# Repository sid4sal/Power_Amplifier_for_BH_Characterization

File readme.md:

# Design and Implementation of High Bandwidth Power Amplifier for B-H Characterization of Magnetic Materials

## Project Overview

The High Bandwidth Power Amplifier is a device for magnetic materials engineers to obtain B-H characterization of magnetic materials at low as well as high frequencies. It is a transformer-less multi-stage direct-coupled linear power amplifier for the characterization of magnetic cores at various frequencies.

The amplifier operates from 50 Hz to 250 kHz with a gain of approximately 4.6 (13.2 dB). It can handle an input power voltage up to ±60 V, allowing the reference signal to be given up to 12-13 V. The current rating of the amplifier is up to 2.5-3 A (continuous).

The user manual and all the required files can be found at this repo.

## Folder Descriptions

- *B-H_curve_plotting_MatLab*: Contains MATLAB files for plotting the simulated B-H curve of the toroid.
  
- *CAD_Outer_Casing_Design*: Includes the design of the outer casing in JPEG format.
  
- *Circuit_Design_and_simulation_results*: Contains the circuit diagrams, stages, and frequency response simulations in both KiCad and Proteus formats. It also includes the PCB design and 3D view, along with potential improvements.
  
- *Demo_and_Experiment_Videos*: Holds videos demonstrating the initial testing of the breadboard circuit, testing of the amplifier on the toroid core, and PCB testing.
  
- *Experiment Results*: Contains experimental results like B-H characteristic data, observed frequency response with load, and primary and secondary voltages at different frequencies.
  
- *Frequency_Response_Observed_vs_Simulated*: Compares the observed and simulated frequency responses in KiCad and Proteus.
  
- *PCB_Design_and_Circuit_Simulation_KiCad*: Placeholder for the KiCad files related to PCB design and circuit simulation.
  
- *Simulation_Proteus*: Placeholder for the Proteus simulation files.

## Additional Documents

- *Circuit_Diagram.png*: Circuit diagram of the power amplifier.
  
- *PCB.jpeg* & *PCB2.jpeg*: Images of the PCB design.
  
- *Project_Problem_Statement.docx*: Detailed problem statement of the project.
  
- *Toroidal_core_design_and_calculation.pdf*: Design and calculations related to the toroidal core.
  
- *Toroid_Core_Detailed_Calculations.pdf*: Detailed calculations for the toroidal core.
  
- *User Manual for Power Amplifier.pdf*: User manual for operating the power amplifier.

Feel free to reach out to me for any clarifications or further details. my contact details can be found inside the user manual.

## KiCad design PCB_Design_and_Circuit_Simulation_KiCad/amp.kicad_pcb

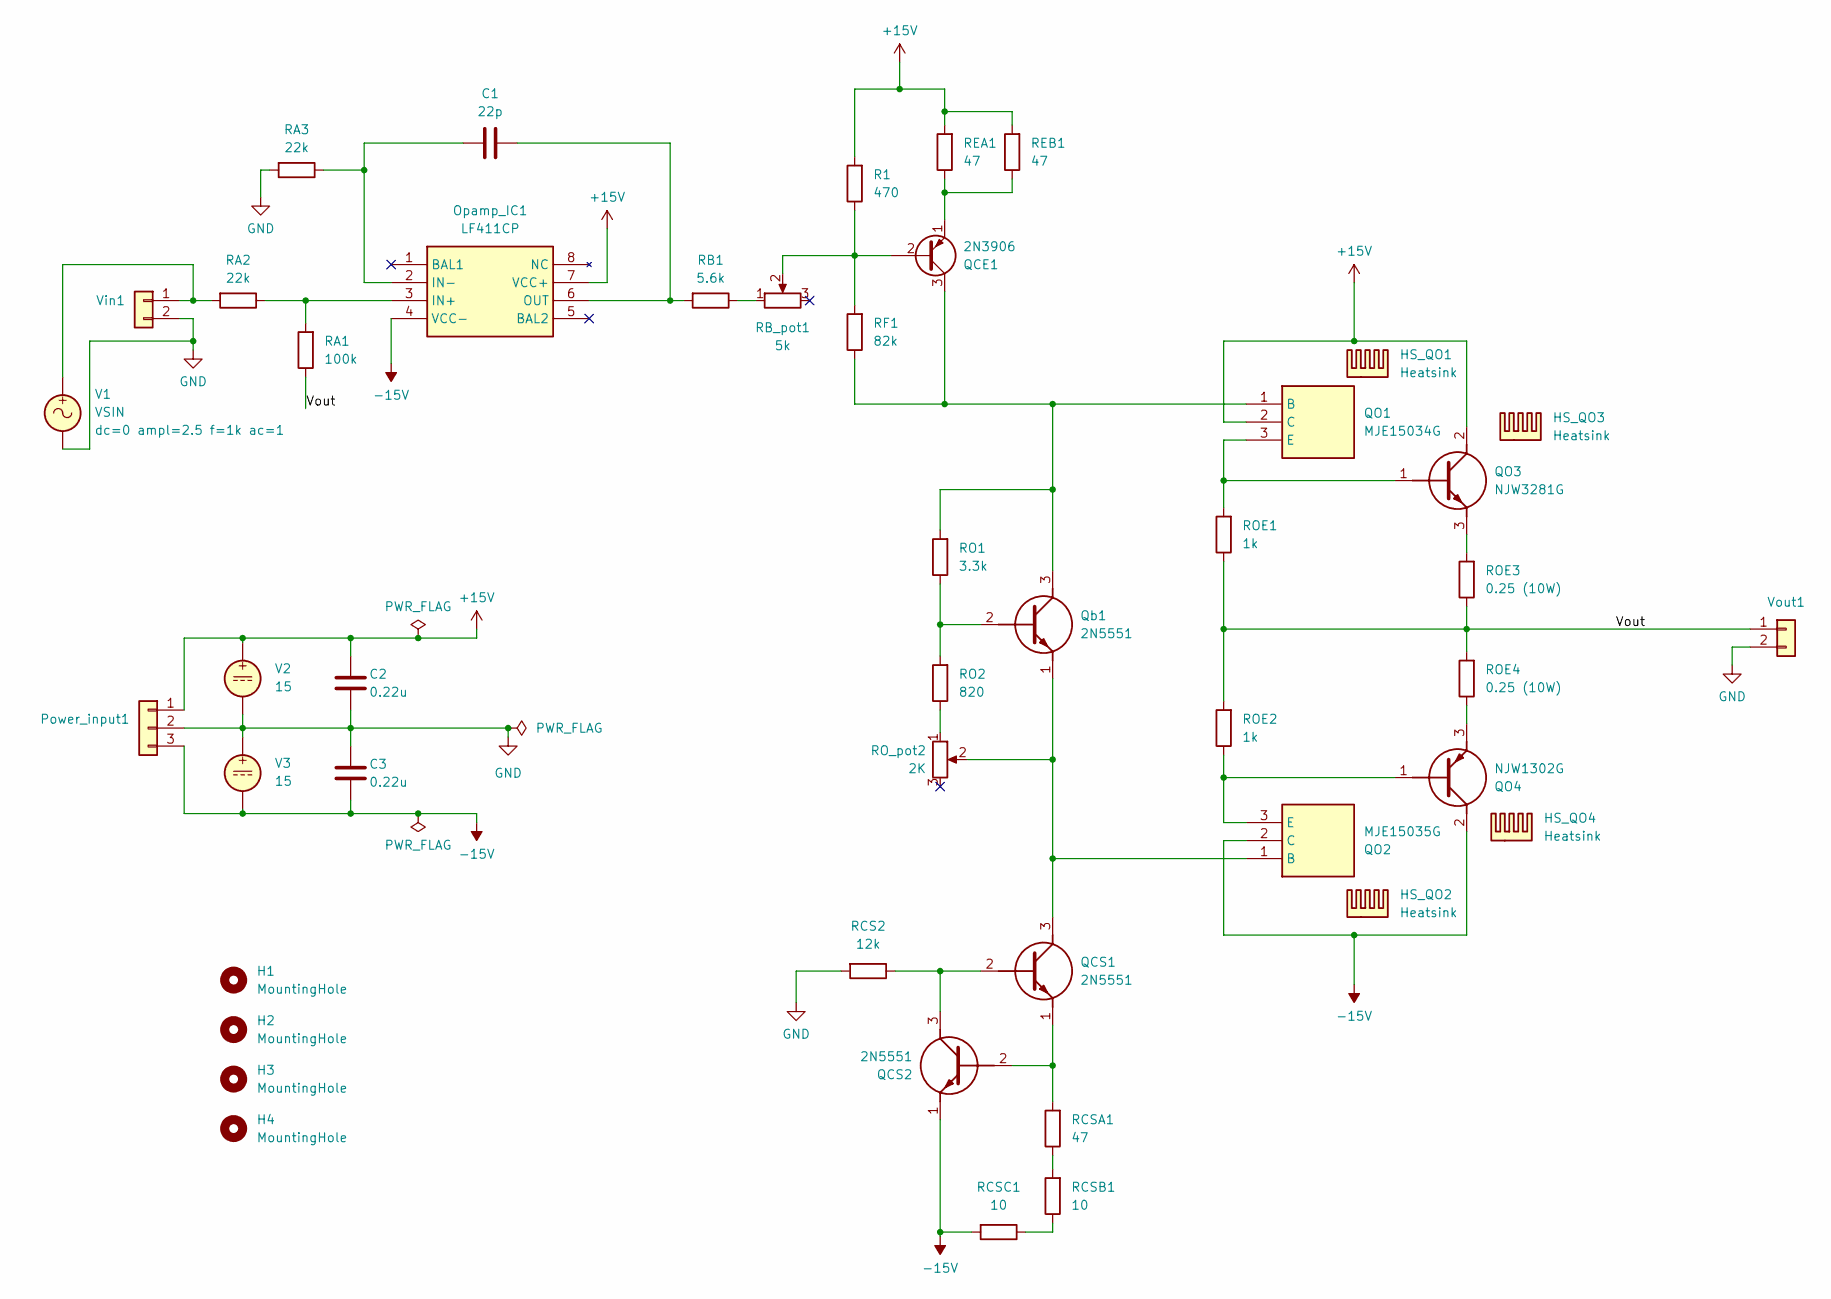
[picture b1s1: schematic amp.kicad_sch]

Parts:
C1: 22p; C_Disc_D3.8mm_W2.6mm_P2.50mm
C2, C3: 0.22u; C_Rect_L7.0mm_W2.0mm_P5.00mm
H1, H2, H3, H4: MountingHole; MountingHole_3mm
HS_QO1, HS_QO2: Heatsink; Heatsink_Stonecold_HS-S03_13.21x12.7mm
HS_QO3, HS_QO4: Heatsink; Heatsink_Fischer_SK129-STS_42x25mm_2xDrill2.5mm
Opamp_IC1: LF411CP; DIP-8_W7.62mm_Socket_LongPads; Mouser Part Number 595-LF411CP
Power_input1: Conn_01x03; PinHeader_1x03_P2.54mm_Vertical
QCE1: 2N3906; TO-92L_Inline_Wide
QCS1, QCS2: 2N5551; TO-92L_Inline_Wide; Mouser Part Number 863-2N5551
QO1: MJE15034G; TO254P483X1010X2035-3P; Mouser Part Number 863-MJE15034G
QO2: MJE15035G; TO254P483X1010X2035-3P; Mouser Part Number 863-MJE15035G
QO3: NJW3281G; TO545P500X1560X2380-3P; Mouser Part Number 863-NJW3281G
QO4: NJW1302G; TO545P500X1560X2380-3P; Mouser Part Number 863-NJW1302G
Qb1: 2N5551; TO-92L_Inline_Wide; Mouser Part Number 863-2N5551
R1: 470; R_Axial_DIN0309_L9.0mm_D3.2mm_P12.70mm_Horizontal
RA1: 100k; R_Axial_DIN0309_L9.0mm_D3.2mm_P12.70mm_Horizontal
RA2, RA3: 22k; R_Axial_DIN0309_L9.0mm_D3.2mm_P12.70mm_Horizontal
RB1: 5.6k; R_Axial_DIN0309_L9.0mm_D3.2mm_P12.70mm_Horizontal
RB_pot1: 5k; Potentiometer_Bourns_3386P_Vertical
RCS2: 12k; R_Axial_DIN0309_L9.0mm_D3.2mm_P12.70mm_Horizontal
RCSA1: 47; R_Axial_DIN0309_L9.0mm_D3.2mm_P12.70mm_Horizontal
RCSB1: 10; R_Axial_DIN0309_L9.0mm_D3.2mm_P12.70mm_Horizontal
RCSC1: 10; R_Axial_DIN0309_L9.0mm_D3.2mm_P12.70mm_Horizontal
REA1: 47; R_Axial_DIN0309_L9.0mm_D3.2mm_P12.70mm_Horizontal
REB1: 47; R_Axial_DIN0309_L9.0mm_D3.2mm_P12.70mm_Horizontal
RF1: 82k; R_Axial_DIN0309_L9.0mm_D3.2mm_P12.70mm_Horizontal
RO1: 3.3k; R_Axial_DIN0309_L9.0mm_D3.2mm_P12.70mm_Horizontal
RO2: 820; R_Axial_DIN0309_L9.0mm_D3.2mm_P12.70mm_Horizontal
ROE1, ROE2: 1k; R_Axial_DIN0309_L9.0mm_D3.2mm_P12.70mm_Horizontal
ROE3, ROE4: 0.25 (10W); R_Axial_Power_L38.0mm_W9.0mm_P40.64mm
RO_pot2: 2K; Potentiometer_Bourns_3386P_Vertical
V1: VSIN
V2, V3: 15
Vin1: Conn_01x02; PinHeader_1x02_P2.54mm_Vertical
Vout1: Conn_01x02; PinHeader_1x02_P2.54mm_Vertical

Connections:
+15V: C2.1, Opamp_IC1.7 (VCC+), Power_input1.1, QO1.2 (C), QO3.2 (C), R1.2, REA1.2, REB1.2, V2.1
-15V: C3.2, Opamp_IC1.4 (VCC-), Power_input1.3, QCS2.1 (E), QO2.2 (C), QO4.2 (C), RCSC1.2, V3.2
/Vout: RA1.1, ROE1.1, ROE2.2, ROE3.1, ROE4.2, Vout1.1
GND: C2.2, C3.1, Power_input1.2, RA3.2, RCS2.2, V1.2, V2.2, V3.1, Vin1.2, Vout1.2
unnamed: Opamp_IC1.3 (IN+), RA1.2, RA2.1
unnamed: C1.1, Opamp_IC1.2 (IN-), RA3.1
unnamed: C1.2, Opamp_IC1.6 (OUT), RB1.2
unnamed: QCE1.2 (B), R1.1, RB_pot1.2, RF1.2
unnamed: QCE1.3 (C), QO1.1 (B), Qb1.3 (C), RF1.1, RO1.2
unnamed: QCE1.1 (E), REA1.1, REB1.1
unnamed: QCS1.2 (B), QCS2.3 (C), RCS2.1
unnamed: QCS1.3 (C), QO2.1 (B), Qb1.1 (E), RO_pot2.2
unnamed: QCS1.1 (E), QCS2.2 (B), RCSA1.2
unnamed: QO1.3 (E), QO3.1 (B), ROE1.2
unnamed: QO2.3 (E), QO4.1 (B), ROE2.1
unnamed: QO3.3 (E), ROE3.2
unnamed: QO4.3 (E), ROE4.1
unnamed: Qb1.2 (B), RO1.1, RO2.2
unnamed: RB1.1, RB_pot1.1
unnamed: RCSA1.1, RCSB1.2
unnamed: RCSB1.1, RCSC1.1
unnamed: RO2.1, RO_pot2.1
unnamed: RA2.2, V1.1, Vin1.1

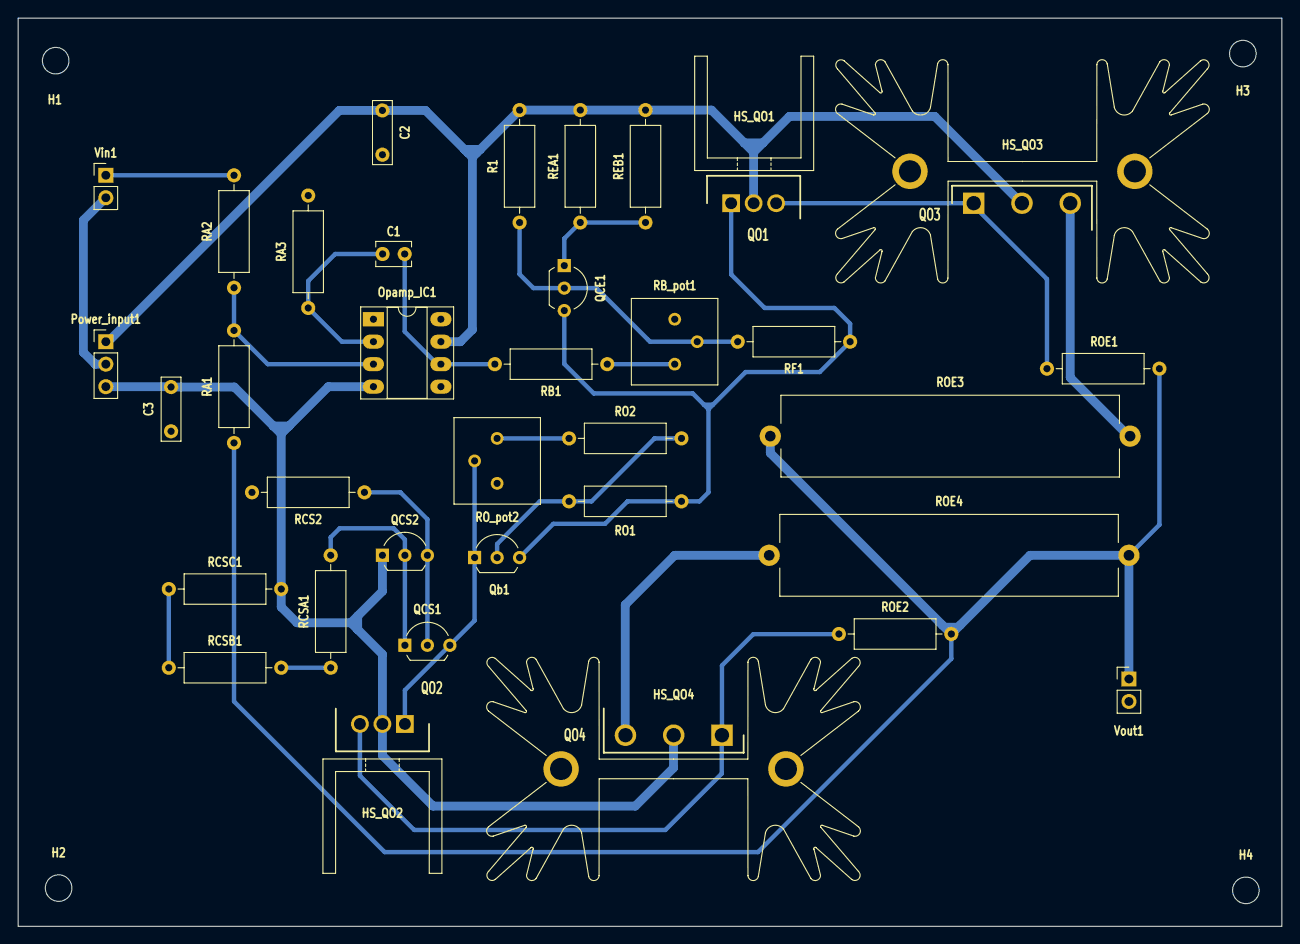
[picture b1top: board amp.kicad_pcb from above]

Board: 2 copper layers, 142.7 x 102.6 mm, 43 parts (0 on the bottom side), 23 nets.
